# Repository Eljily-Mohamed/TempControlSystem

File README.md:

# Objectifs du Projet

Notre mission lors de ce projet d'Instrumentation et Puissance des Systèmes (IPS) a été de concevoir un système d'asservissement de température pour une résistance chauffante. L'objectif principal est de mesurer et réguler précisément la température à l'aide d'une thermistance et d'un capteur de courant.

## **Objectifs Détaillés**

À partir du cahier des charges, nous nous sommes répartis les différentes tâches. L'objectif final est de :

- Concevoir un système de mesure complet permettant de relever des données telles que la température et le courant consommé par la résistance.
- Réguler la température en ajustant la puissance appliquée à la résistance chauffante via un MOSFET, en fonction des mesures effectuées.
- La mise en œuvre d’un **capteur de courant ACS712** pour surveiller la puissance consommée par la résistance chauffante.  
- Analyser les résultats obtenus pour les comparer avec les prévisions théoriques issues de l'équation de la chaleur.
- Étudier l'influence de la convection forcée en utilisant un ventilateur pour améliorer la dissipation thermique.

## **Schéma Fonctionnel**

Pour atteindre nos objectifs, nous avons établi un schéma fonctionnel décrivant le fonctionnement global du système. Ce schéma comprend :

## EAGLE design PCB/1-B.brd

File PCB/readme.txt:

🔧 Modifications nécessaires pour le PCB :

    Le PCB actuel n'est pas le design final. Il manque des connexions importantes pour le fonctionnement correct pour capteur courant.

    Alimentation :
        Ajoutez une alimentation commune pour le +5V nécessaire aux AOP.
        Il y a deux broches importantes : IP+ et IP-. Connectez :
            Le drain du MOSFET à IP+.
            IP- à la résistance chauffante.

    Choix des résistances pour le pont :
        Les valeurs des résistances doivent être proches de la résistance R0 de la thermistance.
        Dans le code C, une fonction calcule la résistance de la thermistance en fonction des résistances R1, R2, et R3, grâce à la loi du pont (vue en cours).
        Le pont est constitué de 4 résistances :
            Thermistance, R1, R2, et R3.

    Résistance pull-down :
        La résistance pull-down connectée au MOSFET doit être placée entre le drain et la gate.
        Vous pouvez souder cette résistance directement sans l'ajouter au PCB.
        Une valeur de 10 kΩ est bonne, mais pas obligatoire. Vous pouvez ajuster selon le besoin.

    Transistor et alimentation :
        Alimentez le transistor avec une tension de 24V.
        Pour le transistor utilisé ici :
            La broche source est au centre.
            Les autres sont drain et gate (voir le PCB).

    Configuration de la gate (PWM) :
        Vous pouvez modifier la broche de la gate pour qu’elle soit connectée à D13.
        Si ce n’est pas le cas, après réception du PCB, vous pouvez réaliser un pontage avec un câble reliant D13 à la broche utilisée.
        Dans le code, j’utilise D13 pour générer un signal PWM.

👉 Si vous avez besoin d’autres précisions ou d’un choix spécifique, faites-moi signe !

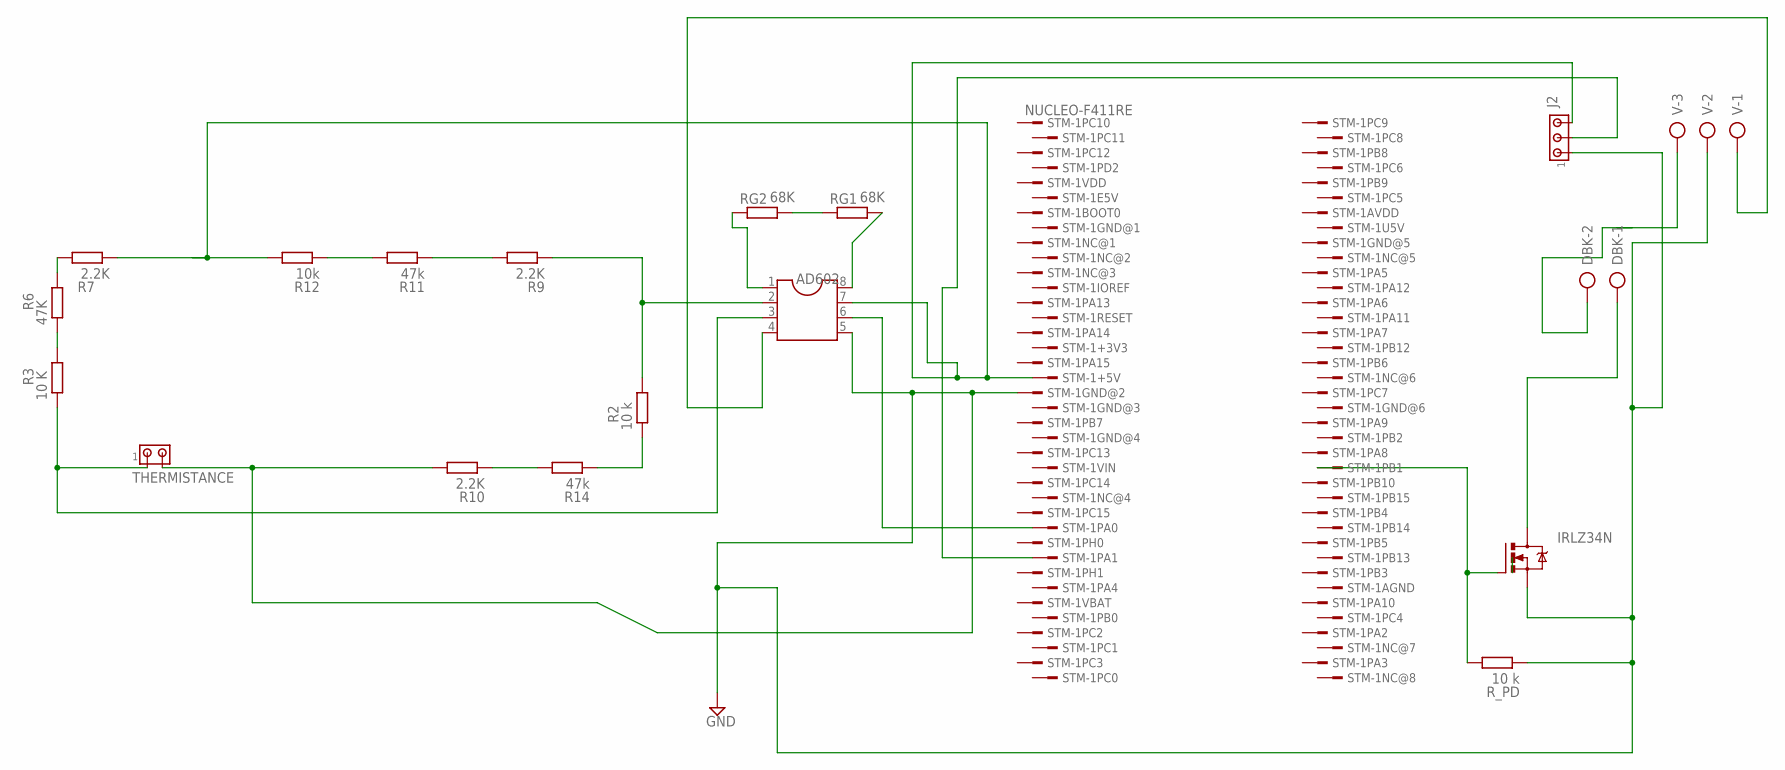
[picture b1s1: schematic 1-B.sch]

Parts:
AD602: DIL8; DIL08
DBK: AK500/2-H
IRLZ34N: IRLZ44Z; TO220BH
J2: MTA03-100; 10X03MTA
R2: 10 k; 0207/7
R3: 10 K; 0207/7
R6: 47K; 0207/7
R7, R9, R10: 2.2K; 0207/7
R11, R14: 47k; 0207/7
R12: 10k; 0207/7
RG1, RG2: 68K; 0207/7
R_PD: 10 k; 0207/7
STM-1: NUCLEO-F411RE; CONN_STM32_NUCLEO
THERMISTANCE: MTA02-156; 1X2MTA
V: AK500/3-H

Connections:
GND: AD602.5, IRLZ34N.S, J2.1, R10.2, R_PD.1, STM-1.19, THERMISTANCE.2, V.2
unnamed: R3.2, R6.1
unnamed: J2.2, STM-1.30
unnamed: AD602.8, RG1.2
unnamed: AD602.1, RG2.1
unnamed: IRLZ34N.G, R_PD.2, STM-1.62
unnamed: AD602.7, J2.3, R7.1, R12.2, STM-1.18
unnamed: DBK.2, V.3
unnamed: DBK.1, IRLZ34N.D
unnamed: RG1.1, RG2.2
unnamed: AD602.6, STM-1.28
unnamed: AD602.3, R3.1, THERMISTANCE.1
unnamed: AD602.4, V.1
unnamed: R6.2, R7.2
unnamed: AD602.2, R2.2, R9.1
unnamed: R9.2, R11.1
unnamed: R11.2, R12.1
unnamed: R2.1, R14.1
unnamed: R10.1, R14.2

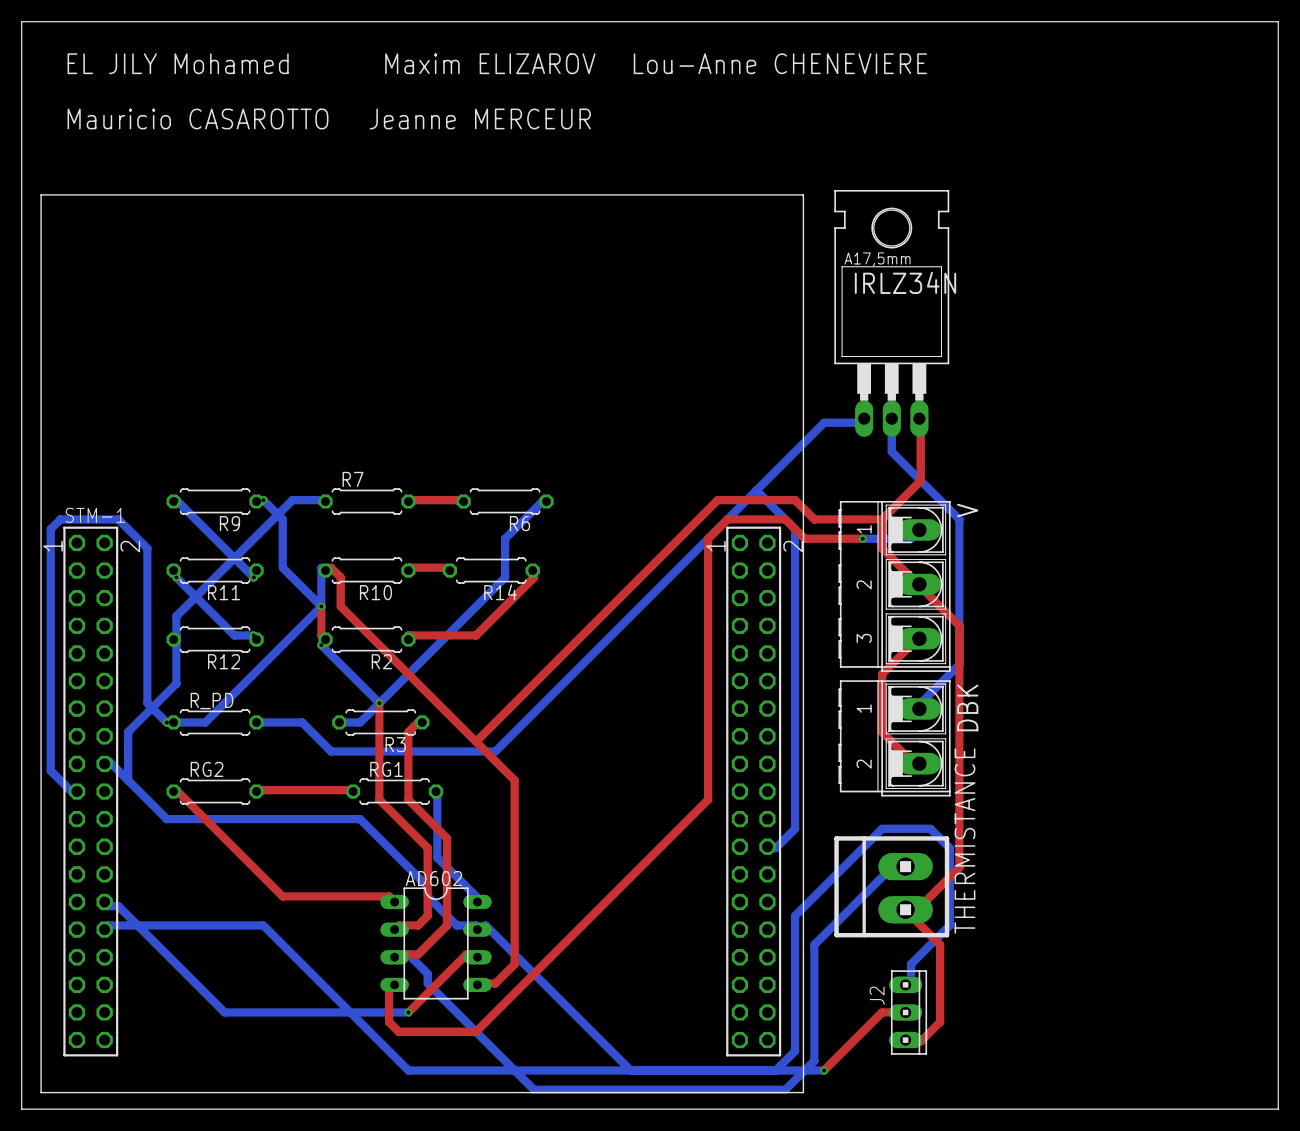
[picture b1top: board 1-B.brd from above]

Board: 2 copper layers, 115.5 x 100.0 mm, 19 parts (0 on the bottom side), 19 nets.
